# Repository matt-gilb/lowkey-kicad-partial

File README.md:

# LowKey36 by Matt Gilbert

This is the ZMK source repo for the LowKey36 spit keyboard.

## This is a prototype!

This repo holds the basic KiCAD files I used to create the prototype of the LowKey36 (v1.2), but it doesn't have all the component symbols/footprints included. As a result you will probably get errors trying to open/edit the PCB design.

Once I have the public-ready v2.0 procduced, I will remove this repo to avoid confusion. For now I'm sharing it for those who are curious.

You can find the ZMK files for the LowKey36 [here](https://github.com/matt-gilb/zmk-config-lowkey36.git).

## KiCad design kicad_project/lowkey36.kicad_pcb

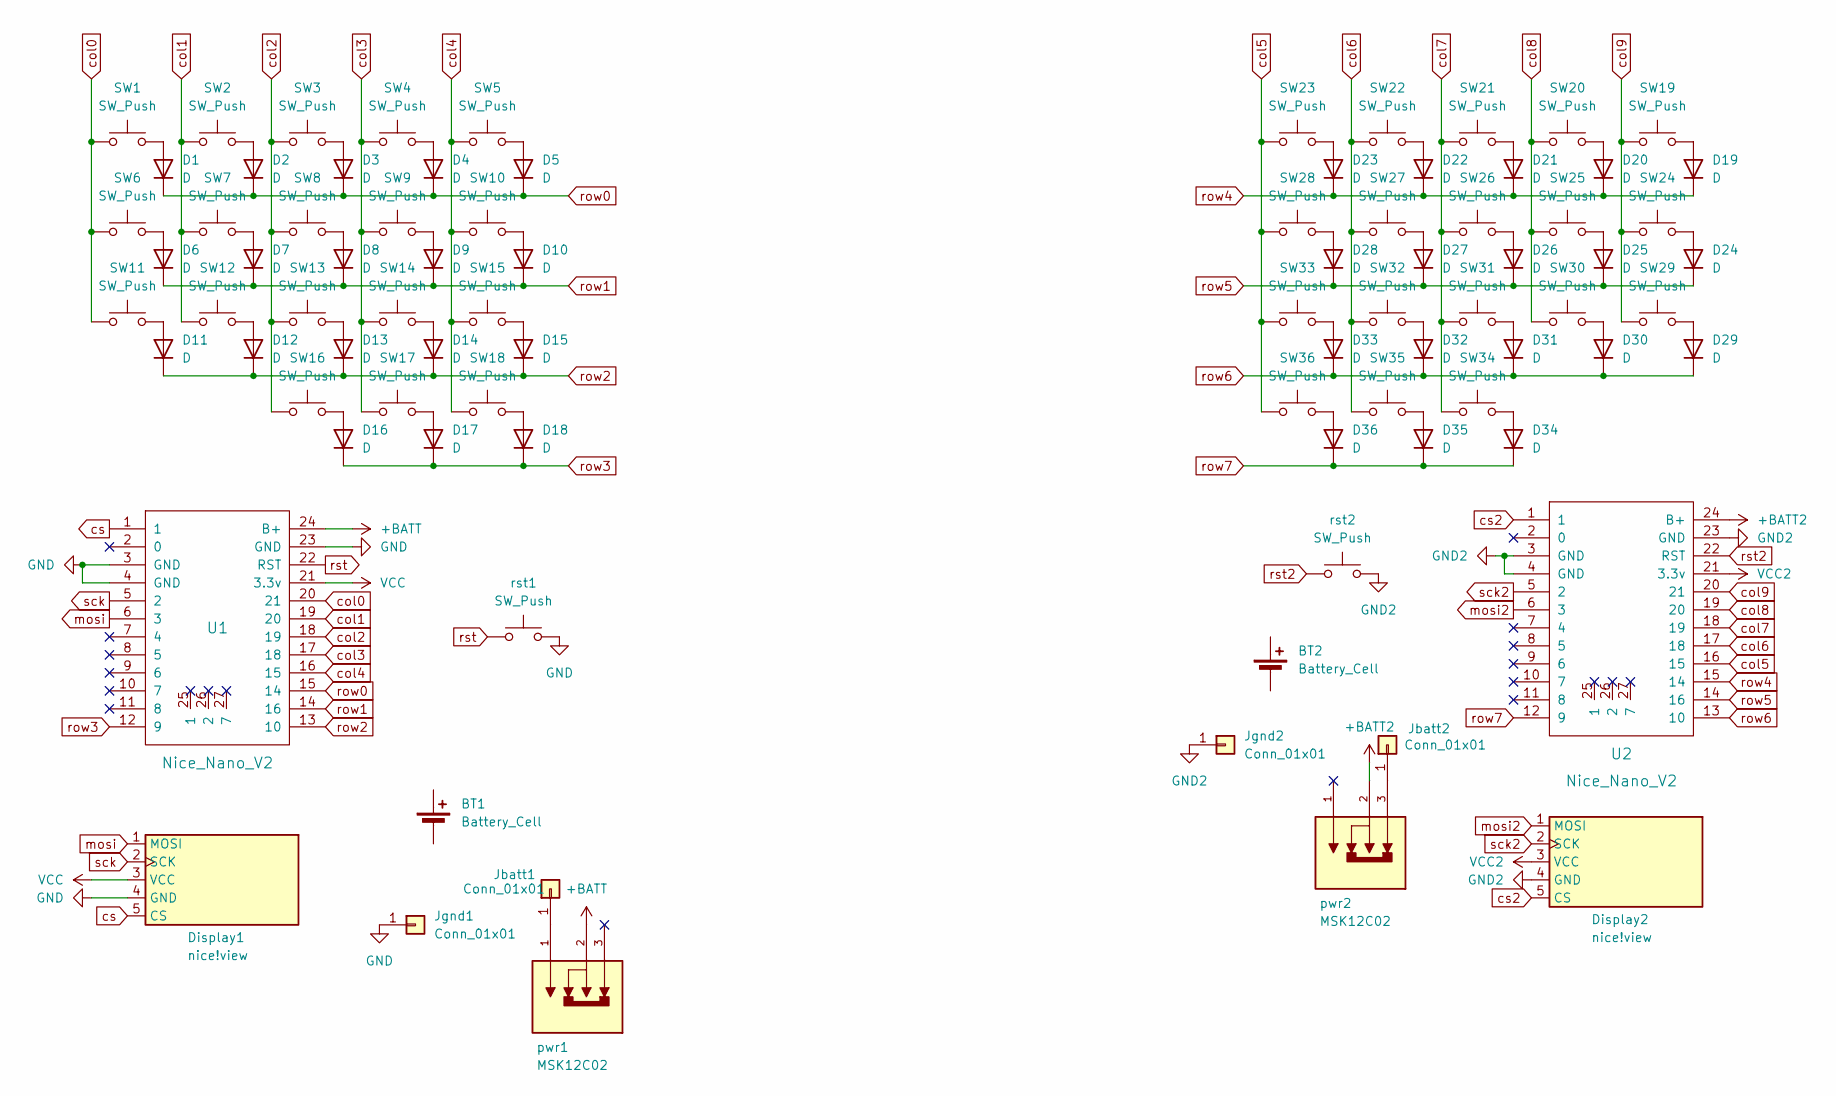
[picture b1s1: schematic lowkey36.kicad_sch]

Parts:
BT1, BT2: Battery_Cell
D1, D2, D3, D4, D5, D6, D7, D8, D9, D10, D11, D12, D13, D14, D15, D16, D17, D18, D19, D20, D21, D22, D23, D24, D25, D26, D27, D28, D29, D30, D31, D32, D33, D34, D35, D36: D; D_SOD-123
Display1, Display2: nice!view; nice_view
Jbatt1, Jbatt2: Conn_01x01; SolderWirePad_1x01_SMD_1x2mm
Jgnd1, Jgnd2: Conn_01x01; SolderWirePad_1x01_SMD_1x2mm
SW1, SW2, SW3, SW4, SW5, SW6, SW7, SW8, SW9, SW10, SW11, SW12, SW13, SW14, SW15, SW16, SW19, SW20, SW21, SW22, SW23, SW24, SW25, SW26, SW27, SW28, SW29, SW30, SW31, SW32, SW33, SW34: SW_Push; CPG1316S01D02
SW17, SW18, SW35, SW36: SW_Push; CPG1316S-1.5w
U1: Nice_Nano_V2
U2: Nice_Nano_V2; nice_nano
pwr1, pwr2: MSK12C02; SW_SSSS811101; PARTREV N/A
rst1, rst2: SW_Push; Panasonic_EVQPUJ_EVQPUA

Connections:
+BATT: U1.24 (B+), pwr1.2
+BATT2: U2.24 (B+), pwr2.2
GND: Display1.4 (GND), Jgnd1.1, U1.3 (GND), U1.4 (GND), U1.23 (GND), rst1.2
GND2: Display2.4 (GND), Jgnd2.1, U2.3 (GND), U2.4 (GND), U2.23 (GND), rst2.2
unnamed: D1.2 (A), SW1.2
unnamed: D2.2 (A), SW2.2
unnamed: D3.2 (A), SW3.2
unnamed: D4.2 (A), SW4.2
unnamed: D5.2 (A), SW5.2
unnamed: D6.2 (A), SW6.2
unnamed: D7.2 (A), SW7.2
unnamed: D8.2 (A), SW8.2
unnamed: D9.2 (A), SW9.2
unnamed: D10.2 (A), SW10.2
unnamed: D11.2 (A), SW11.2
unnamed: D12.2 (A), SW12.2
unnamed: D13.2 (A), SW13.2
unnamed: D14.2 (A), SW14.2
unnamed: D15.2 (A), SW15.2
unnamed: D16.2 (A), SW16.2
unnamed: D17.2 (A), SW17.2
unnamed: D18.2 (A), SW18.2
unnamed: D19.2 (A), SW19.2
unnamed: D20.2 (A), SW20.2
unnamed: D21.2 (A), SW21.2
unnamed: D22.2 (A), SW22.2
unnamed: D23.2 (A), SW23.2
unnamed: D24.2 (A), SW24.2
unnamed: D25.2 (A), SW25.2
unnamed: D26.2 (A), SW26.2
unnamed: D27.2 (A), SW27.2
unnamed: D28.2 (A), SW28.2
unnamed: D29.2 (A), SW29.2
unnamed: D30.2 (A), SW30.2
unnamed: D31.2 (A), SW31.2
unnamed: D32.2 (A), SW32.2
unnamed: D33.2 (A), SW33.2
unnamed: D34.2 (A), SW34.2
unnamed: D35.2 (A), SW35.2
unnamed: D36.2 (A), SW36.2
unnamed: Jbatt1.1, pwr1.1
unnamed: Jbatt2.1, pwr2.3
VCC: Display1.3 (VCC), U1.21 (3.3v)
VCC2: Display2.3 (VCC), U2.21 (3.3v)
col0: SW1.1, SW6.1, SW11.1, U1.20 (21)
col1: SW2.1, SW7.1, SW12.1, U1.19 (20)
col2: SW3.1, SW8.1, SW13.1, SW16.1, U1.18 (19)
col3: SW4.1, SW9.1, SW14.1, SW17.1, U1.17 (18)
col4: SW5.1, SW10.1, SW15.1, SW18.1, U1.16 (15)
col5: SW23.1, SW28.1, SW33.1, SW36.1, U2.16 (15)
col6: SW22.1, SW27.1, SW32.1, SW35.1, U2.17 (18)
col7: SW21.1, SW26.1, SW31.1, SW34.1, U2.18 (19)
col8: SW20.1, SW25.1, SW30.1, U2.19 (20)
col9: SW19.1, SW24.1, SW29.1, U2.20 (21)
cs: Display1.5 (CS), U1.1
cs2: Display2.5 (CS), U2.1
mosi: Display1.1 (MOSI), U1.6 (3)
mosi2: Display2.1 (MOSI), U2.6 (3)
row0: D1.1 (K), D2.1 (K), D3.1 (K), D4.1 (K), D5.1 (K), U1.15 (14)
row1: D6.1 (K), D7.1 (K), D8.1 (K), D9.1 (K), D10.1 (K), U1.14 (16)
row2: D11.1 (K), D12.1 (K), D13.1 (K), D14.1 (K), D15.1 (K), U1.13 (10)
row3: D16.1 (K), D17.1 (K), D18.1 (K), U1.12 (9)
row4: D19.1 (K), D20.1 (K), D21.1 (K), D22.1 (K), D23.1 (K), U2.15 (14)
row5: D24.1 (K), D25.1 (K), D26.1 (K), D27.1 (K), D28.1 (K), U2.14 (16)
row6: D29.1 (K), D30.1 (K), D31.1 (K), D32.1 (K), D33.1 (K), U2.13 (10)
row7: D34.1 (K), D35.1 (K), D36.1 (K), U2.12 (9)
rst: U1.22 (RST), rst1.1
rst2: U2.22 (RST), rst2.1
sck: Display1.2 (SCK), U1.5 (2)
sck2: Display2.2 (SCK), U2.5 (2)

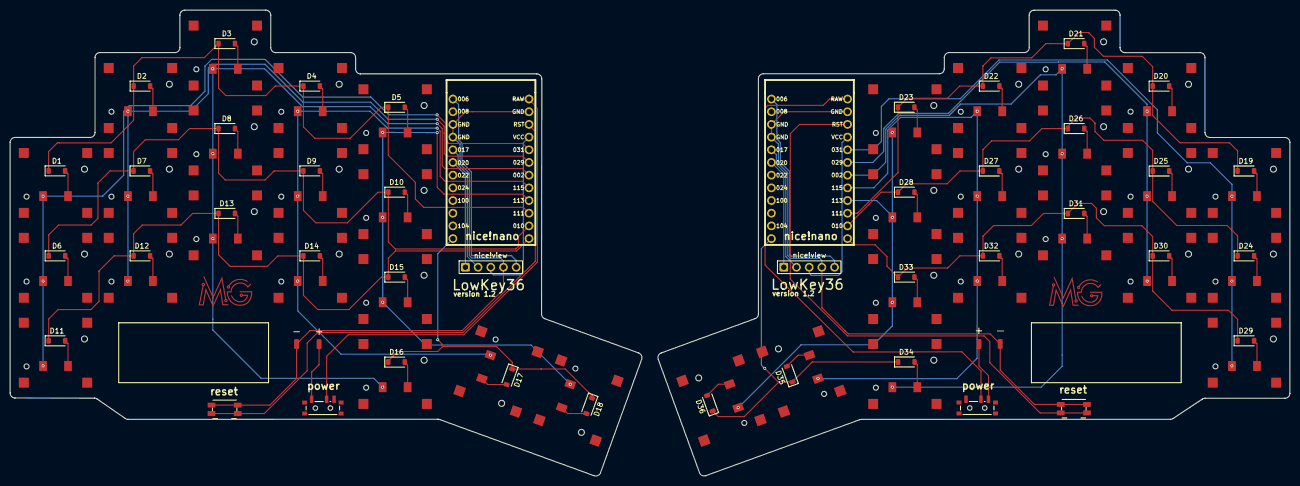
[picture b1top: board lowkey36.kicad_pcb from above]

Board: 2 copper layers, 256.2 x 93.2 mm, 84 parts (0 on the bottom side), 70 nets.

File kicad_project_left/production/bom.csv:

Designator,Footprint,Quantity,Value,LCSC Part #
"D1, D10, D11, D12, D13, D14, D15, D16, D17, D18, D2, D3, D4, D5, D6, D7, D8, D9",D_SOD-123,18,D,
DISPLAY1,nice_view,1,nice!view,
"JBATT1, JGND1",SolderWirePad_1x01_SMD_1x2mm,2,Conn_01x01,
PWR1,SW_SSSS811101,1,MSK12C02,
RST1,Panasonic_EVQPUJ_EVQPUA,1,SW_Push,
"SW1, SW10, SW11, SW12, SW13, SW14, SW15, SW16, SW2, SW3, SW4, SW5, SW6, SW7, SW8, SW9",CPG1316S01D02,16,SW_Push,
"SW17, SW18",CPG1316S-1.5w,2,SW_Push,
U1,nice_nano,1,Nice_Nano_V2,

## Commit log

2024-12-07 set up git
2024-12-07 add readme
